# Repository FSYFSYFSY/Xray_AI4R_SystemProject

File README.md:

# AI For Robotics ELEN90095

Software for running the robot that is the focus of the AI For Robotics Subject

## Setting up ROS Components:

- Ensure you are running a Ubuntu 22.04 LTS either in a virtual machine or natively and install ROS2 Humble following the instructions here: https://docs.ros.org/en/humble/Installation.html
- Clone this repository locally to your computer
- Open a terminal and enter the folder using `cd [path to the repository]/ros2_ws`
- If you have not added `source /opt/ros/humble/setup.bash` to your .bashrc you must run this in each terminal before running ros related commands
- run `sudo rosdep init`
- run `rosdep update`
- run `colcon build`
- run `source install/setup.bash` (this adds the new ros commands to path after building, it also needs to be done in each new terminal so you can add it to your .bashrc however you will need to open a new terminal after using colcon build)

You should now have managed to build the packages.

### Sensor PCB Parser Node
- In order for the parser node to work, you must allow read write access on the computer running ros to the file where the sensor pcb publishes/reads data. This file is located at /dev/ttyACM0 or /dev/ttyACM1
- To do this we add a udev rule for each file
- Create a file ttyACM0.rules containing `KERNEL=="ttyACM0", MODE="0666"` at /etc/udev/rules.d/ttyACM0.rules
- Create a file ttyACM1.rules containing `KERNEL=="ttyACM1", MODE="0666"` at /etc/udev/rules.d/ttyACM1.rules

To do that we run the following commands:
- `echo 'KERNEL=="ttyACM0", MODE="0666"' | sudo tee /etc/udev/rules.d/ttyACM0.rules`
- `echo 'KERNEL=="ttyACM1", MODE="0666"' | sudo tee /etc/udev/rules.d/ttyACM1.rules`
- `sudo udevadm control --reload-rules` 
- `sudo udevadm trigger`

### Trouble Shooting:

If you encounter a build error like `Could not find package configuration file provided by "rosidl_default_generators" with any of the following names:" ...` 

The solution is to open a terminal and run `cd [path to the repository]` and then run `sudo chmod 777 -R .` to update permissions to allow full read/write/execute access.

## Setting up Pico SDK Workspace
In order to build the project in the mcu_ws you will need to run the following commands
- cd `[PATH_TO_REPO]/mcu_ws/build`
- cmake .. & make

There will now be two uf2 files within the build folder that can be flashed to each pico respectively. Optionally you may use `make ai4r-sensors-rp1` or `make ai4r-sensors-rp2` to only build the files for respective pico.

To flash the uf2 file to the pico you can hold down the boot button on the pico and then plug it in which will mount it like a storage device, then you copy the uf2 file onto the mounted storage device. Alternatively you can use pico-tool from the Raspberry Pi Foundation. You can run `cmake..; make; sudo picotool load -F [filetoflash].uf2; sudo picotool reboot` from the build folder to automatically build and copy it over, if it fails you will need to manually put it into bootsel mode.

Alternatively you could try use the pico-vscode extension but importing an existing repository does not work properly at this stage due to the different build system (ninja) used!

## Setting up PCB Workspace
The PCB's were designed using KiCAD. This can be downloaded for free and then the project can be directly opened. It may require some manual relinking of the project specific libraries.

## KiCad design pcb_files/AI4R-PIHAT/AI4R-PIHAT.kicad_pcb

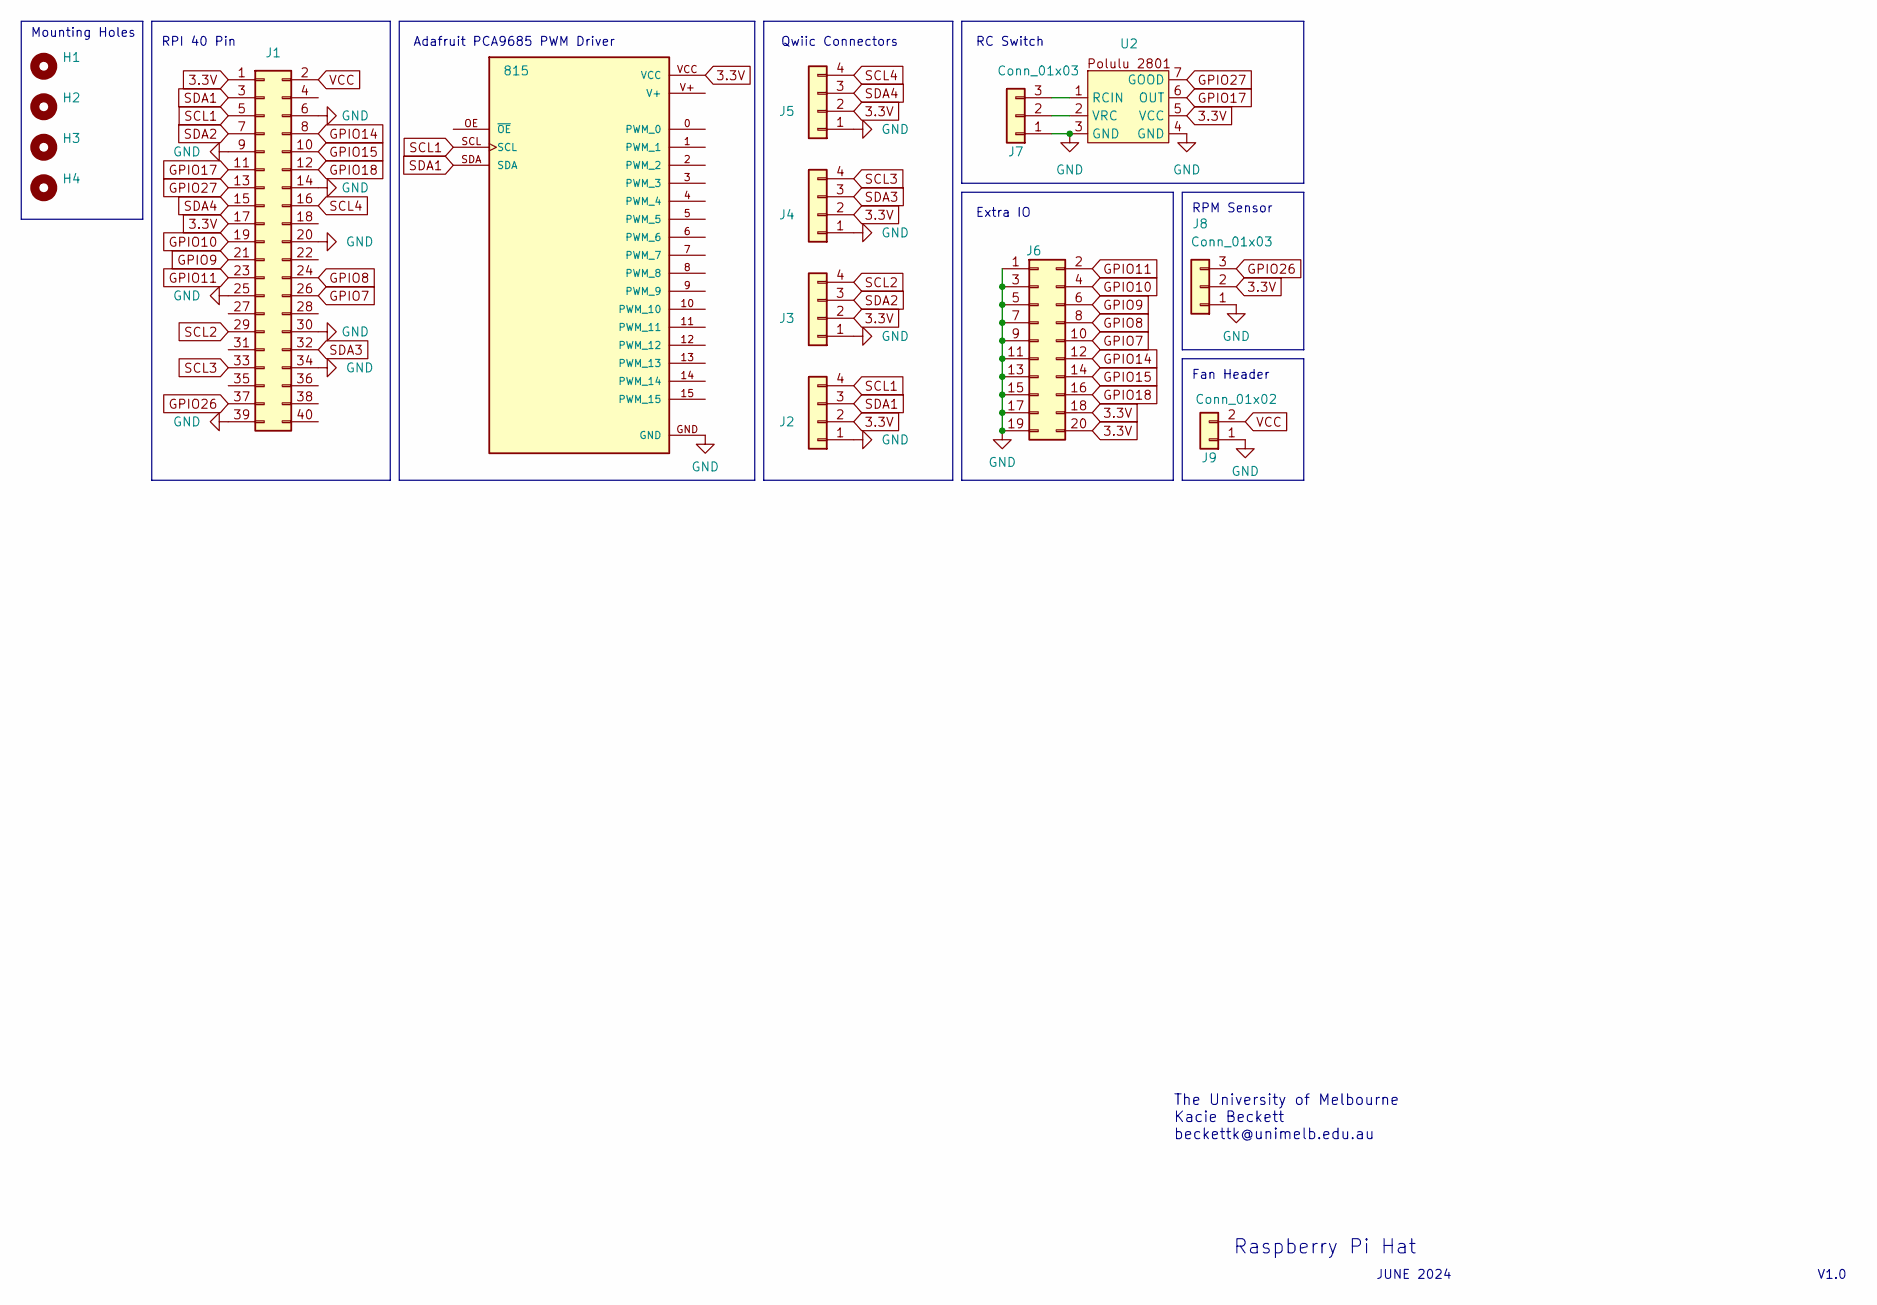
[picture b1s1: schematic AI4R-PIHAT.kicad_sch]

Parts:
H1, H2, H3, H4: MountingHole; MountingHole_2.7mm_M2.5_Pad
J1: Conn_02x20_Odd_Even; PinHeader_2x20_P2.54mm_Vertical
J2, J3, J4, J5: Conn_01x04; JST_SH_SM04B-SRSS-TB_1x04-1MP_P1.00mm_Horizontal
J6: Conn_02x10_Odd_Even; PinHeader_2x10_P2.54mm_Vertical
J7, J8: Conn_01x03; PinHeader_1x03_P2.54mm_Vertical
J9: Conn_01x02; PinHeader_1x02_P2.54mm_Vertical
U1: 815; Polulu-PCA9685; PARTREV C
U2: 2801RCSwitch

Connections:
3.3V: J1.1, J1.17, J2.2, J3.2, J4.2, J5.2, J6.18, J6.20, J8.2, U1.VCC, U2.5 (VCC)
GND: J1.6, J1.9, J1.14, J1.20, J1.25, J1.30, J1.34, J1.39, J2.1, J3.1, J4.1, J5.1, J6.1, J6.3, J6.5, J6.7, J6.9, J6.11, J6.13, J6.15, J6.17, J6.19, J7.1, J8.1, J9.1, U1.GND, U2.3 (GND), U2.4 (GND)
GPIO7: J1.26, J6.10
GPIO8: J1.24, J6.8
GPIO9: J1.21, J6.6
GPIO10: J1.19, J6.4
GPIO11: J1.23, J6.2
GPIO14: J1.8, J6.12
GPIO15: J1.10, J6.14
GPIO17: J1.11, U2.6 (OUT)
GPIO18: J1.12, J6.16
GPIO26: J1.37, J8.3
GPIO27: J1.13, U2.7 (GOOD)
unnamed: J7.2, U2.2 (VRC)
unnamed: J7.3, U2.1 (RCIN)
SCL1: J1.5, J2.4, U1.SCL
SCL2: J1.29, J3.4
SCL3: J1.33, J4.4
SCL4: J1.16, J5.4
SDA1: J1.3, J2.3, U1.SDA
SDA2: J1.7, J3.3
SDA3: J1.32, J4.3
SDA4: J1.15, J5.3
VCC: J1.2, J9.2

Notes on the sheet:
Extra IO
V1.0
Fan Header
Raspberry Pi Hat
Adafruit PCA9685 PWM Driver
RPI 40 Pin
RPM Sensor
RC Switch
JUNE 2024
Qwiic Connectors
The University of Melbourne Kacie Beckett beckettk@unimelb.edu.au
Mounting Holes

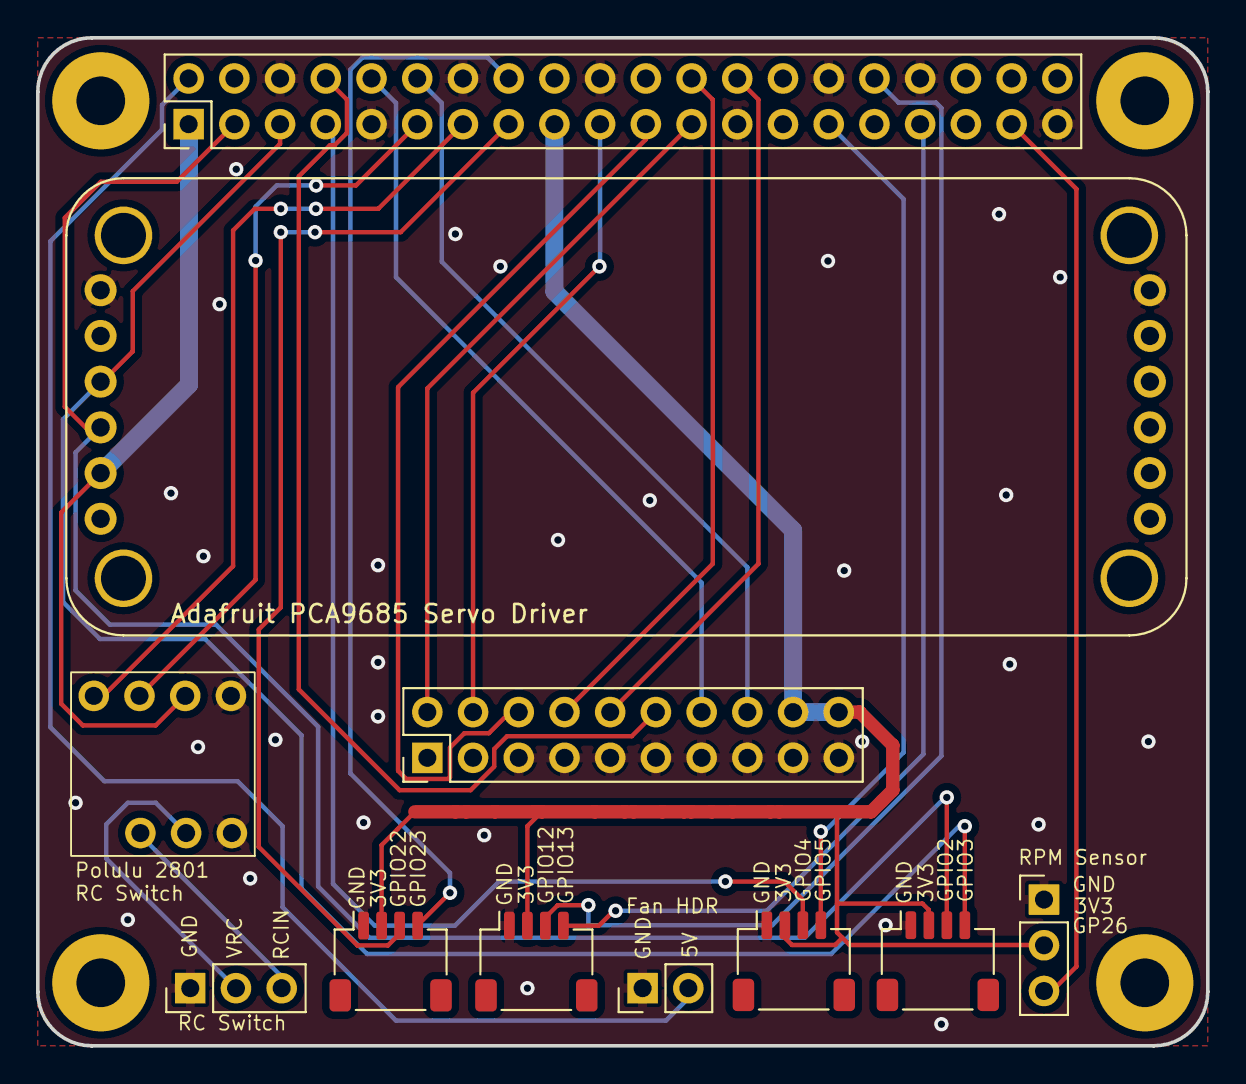
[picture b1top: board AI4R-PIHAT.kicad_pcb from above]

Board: 2 copper layers, 65.0 x 56.0 mm, 15 parts (0 on the bottom side), 24 nets.

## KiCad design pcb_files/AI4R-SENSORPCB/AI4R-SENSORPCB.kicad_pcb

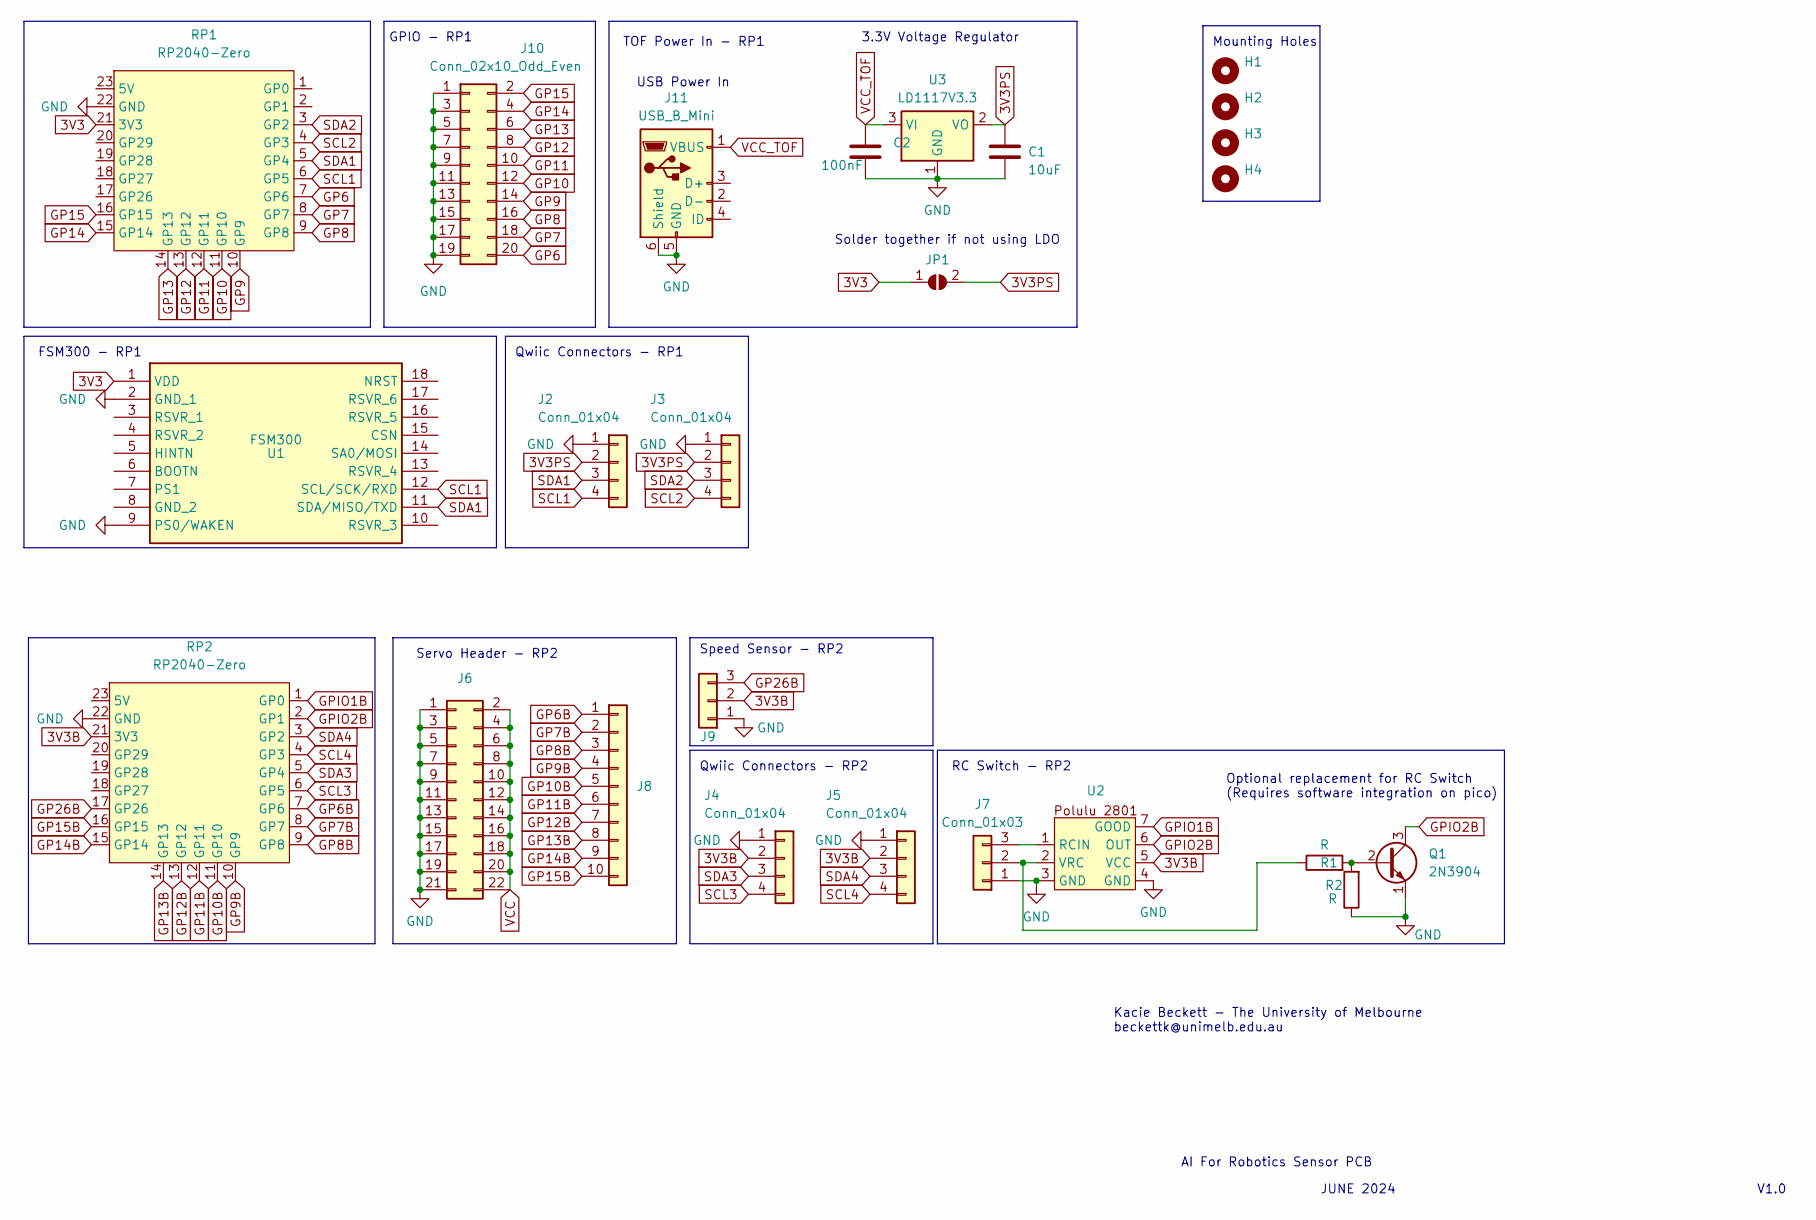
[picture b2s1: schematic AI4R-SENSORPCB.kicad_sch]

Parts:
C1: 10uF; CP_Radial_D4.0mm_P2.00mm
C2: 100nF; CP_Radial_D4.0mm_P2.00mm
H1, H2, H3, H4: MountingHole; MountingHole_3.2mm_M3_DIN965_Pad
J2, J3, J4, J5: Conn_01x04; JST_SH_SM04B-SRSS-TB_1x04-1MP_P1.00mm_Horizontal
J6: Conn_02x11_Odd_Even; PinHeader_2x11_P2.54mm_Vertical
J7, J9: Conn_01x03; PinHeader_1x03_P2.54mm_Vertical
J8: Conn_01x10; PinHeader_1x10_P2.54mm_Vertical
J10: Conn_02x10_Odd_Even; PinHeader_2x10_P2.54mm_Vertical
J11: USB_B_Mini; USB_Mini-B_Lumberg_2486_01_Horizontal
JP1: SolderJumper_2_Open; SolderJumper-2_P1.3mm_Open_Pad1.0x1.5mm
Q1: 2N3904; TO-92_Inline
R1, R2: R; R_0805_2012Metric
RP1, RP2: RP2040-Zero
U1: FSM300; Manufacturer_Part_Number FSM300
U2: 2801RCSwitch
U3: LD1117V3.3; TO-220-3_Vertical

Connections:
3V3: JP1.1 (A), RP1.21 (3V3), U1.1 (VDD)
3V3B: J4.2, J5.2, J9.2, RP2.21 (3V3), U2.5 (VCC)
3V3PS: C1.1, J2.2, J3.2, JP1.2 (B), U3.2 (VO)
GND: C1.2, C2.2, J2.1, J3.1, J4.1, J5.1, J6.1, J6.3, J6.5, J6.7, J6.9, J6.11, J6.13, J6.15, J6.17, J6.19, J6.21, J7.1, J9.1, J10.1, J10.3, J10.5, J10.7, J10.9, J10.11, J10.13, J10.15, J10.17, J10.19, J11.5 (GND), J11.6 (Shield), Q1.1 (E), R2.1, RP1.22 (GND), RP2.22 (GND), U1.2 (GND_1), U1.9 (PS0/WAKEN), U2.3 (GND), U2.4 (GND), U3.1 (GND)
GP6: J10.20, RP1.7 (GP6)
GP6B: J8.1, RP2.7 (GP6)
GP7: J10.18, RP1.8 (GP7)
GP7B: J8.2, RP2.8 (GP7)
GP8: J10.16, RP1.9 (GP8)
GP8B: J8.3, RP2.9 (GP8)
GP9: J10.14, RP1.10 (GP9)
GP9B: J8.4, RP2.10 (GP9)
GP10: J10.12, RP1.11 (GP10)
GP10B: J8.5, RP2.11 (GP10)
GP11: J10.10, RP1.12 (GP11)
GP11B: J8.6, RP2.12 (GP11)
GP12: J10.8, RP1.13 (GP12)
GP12B: J8.7, RP2.13 (GP12)
GP13: J10.6, RP1.14 (GP13)
GP13B: J8.8, RP2.14 (GP13)
GP14: J10.4, RP1.15 (GP14)
GP14B: J8.9, RP2.15 (GP14)
GP15: J10.2, RP1.16 (GP15)
GP15B: J8.10, RP2.16 (GP15)
GP26B: J9.3, RP2.17 (GP26)
GPIO1B: RP2.1 (GP0), U2.7 (GOOD)
GPIO2B: Q1.3 (C), RP2.2 (GP1), U2.6 (OUT)
unnamed: J7.2, R1.1, U2.2 (VRC)
unnamed: J7.3, U2.1 (RCIN)
unnamed: Q1.2 (B), R1.2, R2.2
SCL1: J2.4, RP1.6 (GP5), U1.12 (SCL/SCK/RXD)
SCL2: J3.4, RP1.4 (GP3)
SCL3: J4.4, RP2.6 (GP5)
SCL4: J5.4, RP2.4 (GP3)
SDA1: J2.3, RP1.5 (GP4), U1.11 (SDA/MISO/TXD)
SDA2: J3.3, RP1.3 (GP2)
SDA3: J4.3, RP2.5 (GP4)
SDA4: J5.3, RP2.3 (GP2)
VCC: J6.2, J6.4, J6.6, J6.8, J6.10, J6.12, J6.14, J6.16, J6.18, J6.20, J6.22
VCC_TOF: C2.1, J11.1 (VBUS), U3.3 (VI)

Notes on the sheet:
Kacie Beckett - The University of Melbourne beckettk@unimelb.edu.au
V1.0
USB Power In
RC Switch - RP2
Servo Header - RP2
GPIO - RP1
Qwiic Connectors - RP1
TOF Power In - RP1
FSM300 - RP1
Speed Sensor - RP2
Qwiic Connectors - RP2
AI For Robotics Sensor PCB
Optional replacement for RC Switch (Requires software integration on pico)
3.3V Voltage Regulator
Mounting Holes
JUNE 2024
Solder together if not using LDO

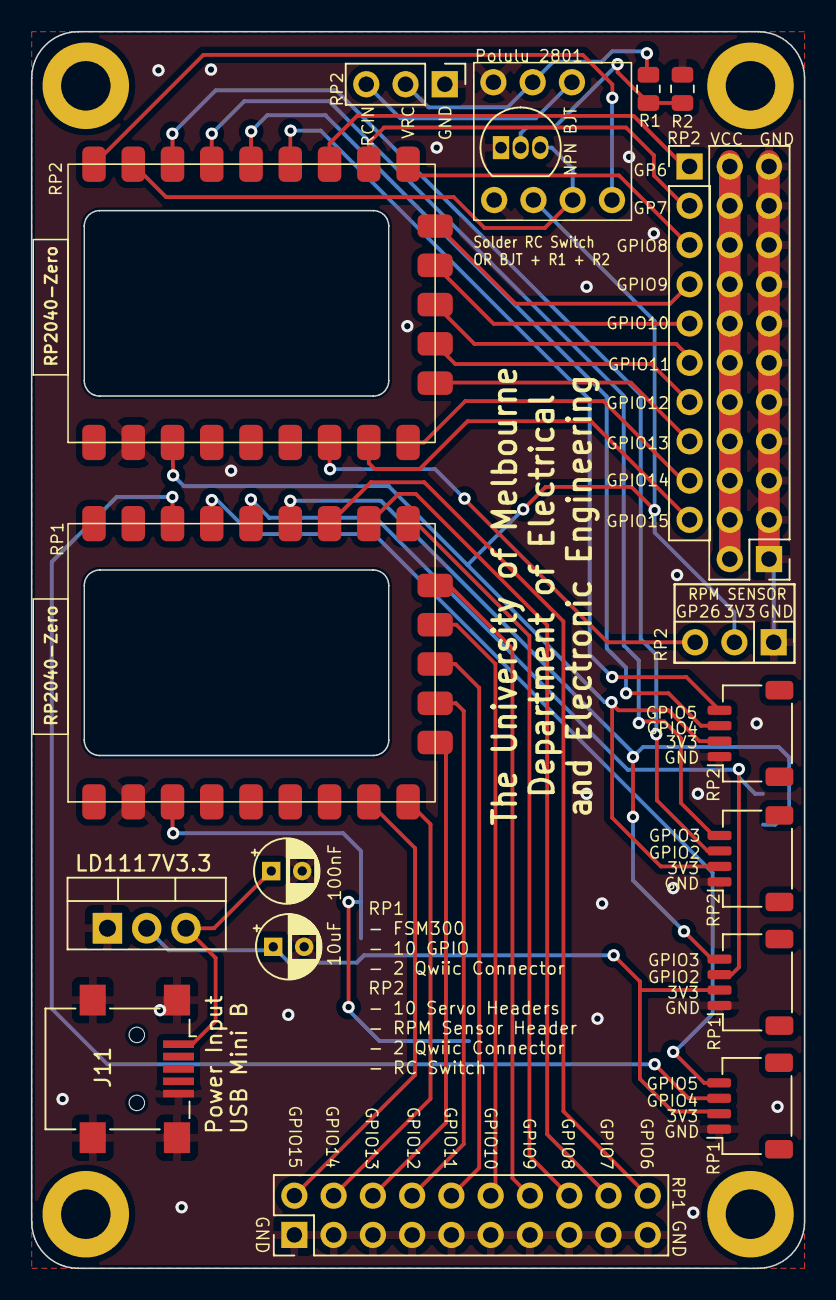
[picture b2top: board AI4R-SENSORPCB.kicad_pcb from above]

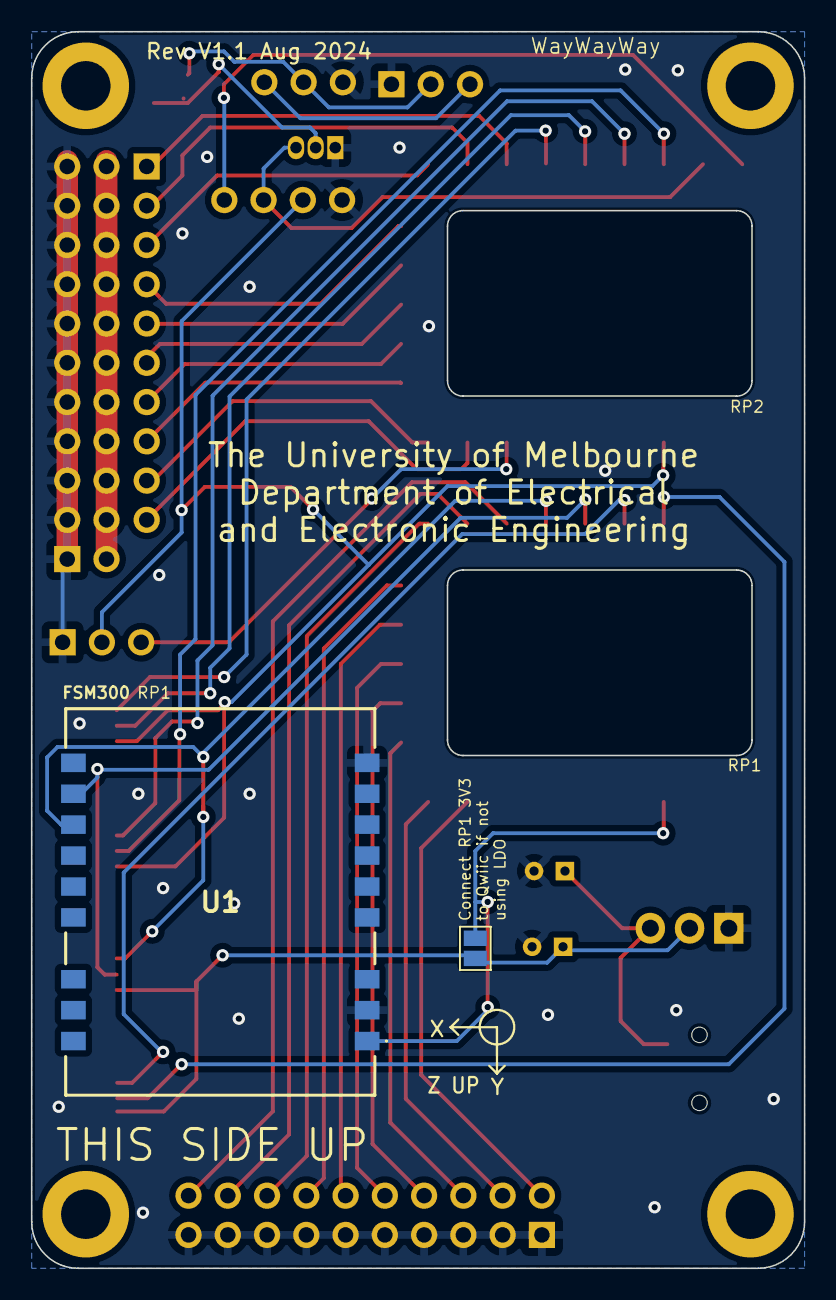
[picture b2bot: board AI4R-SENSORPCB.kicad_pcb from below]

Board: 2 copper layers, 50.0 x 80.0 mm, 25 parts (2 on the bottom side), 40 nets.

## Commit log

2024-09-10 Add Sensor ROS Node and PCB Files
2024-09-10 Upgrades for 2024 including Oak-D nodes, RC Switch Node, Foxglove GUI ROS2 Parameters
2024-09-11 fix cmake merge conflict
2024-09-11 fix sensor node typo
2024-09-18 Fixed steering trim int overflow display bug
2024-09-18 Initial IMU policy changes made by Paul
2024-09-18 Publish imu heading angle on topic 'imu_heading_angle'
2024-09-18 Publish heading angle
2024-09-18 UI changes
2025-09-09 Added further development for the sensoring and acuating via Pi Picos
2025-09-09 Added configs to keep LF line ending cleaner across clones and commits
2025-09-21 Updated to ROS Jazzy and Pico for commanding traxxas and various clean-up
2025-10-21 Added a path prediction function
    Predict path with detected cones.
    Returns a np.poly1d object.
2025-10-21 Changed camera angle in cone_detector_node
    The initial 20 was making cone's z becoming more than 10 under 4 meters.
2025-10-21 Adjusted policy_node to use path_prediction
    Lowered fixed esc percentage as well.
2025-10-21 remove redundant module of path_prediction" "
2025-10-28 New logic of trajectory prediction by using global history record, reduce degree to 3.
    Removed the previous redundant functions, cubric connection, and anchor points addition.
2025-10-28 renew the new version of path_prediction python library
    without plot and test function, the basic logic of history cone record has been shown in .ipynb file with same name, it should be transfer into policy code.
2025-10-30 The interface of path_prediction was redesigned to enable it to be called directly by a single function within the policy, thereby enhancing the code's encapsulation and modularity. The current call 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
2025-10-31 Fix the bug of redundant cubic bridging logic(remoced), fixed some bug about offset
